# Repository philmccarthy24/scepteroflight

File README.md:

# Scepter of Light
## 3D printable prop

*Phil McCarthy, August 2021*

### What is this?
A 3D printed version of the Scepter of Light from Elena of Avalor, created by Phil McCarthy over summer 2021.

### Why?
My daughter loves Elena, and wanted a scepter to go with her costume. I've thought about designing a circuit board and doing some 3D printing for a while - so this was an ideal learning project with the right level of challenge. It took about three months to complete in my spare time.

The scepter lights up and plays music when turned on, and rumbles with "magic" when waved. See a quick [video demo here](https://youtu.be/RlnO9K1_UK8).

I've made [an Instructable](https://www.instructables.com/Scepter-of-Light/) and [a Thing](https://www.thingiverse.com/thing:4937785) to go with this repository, to make it more searchable.

### Features

- Easy access charging via MicroUSB port in unscrewable hilt - red light is charging, blue means charged. Grille around port allows heat dissapation during charge. 

- Custom PCB with ULN2003A driver allows independent control of each of the three side ultrabright LEDs, the top ultrabright LED array, and the vibration motor, via the MCU's output pins.

- All components on the PCB board are through-hole, allowing easy soldering/assembly, but it's thin enough to fit into the 50mm diameter scepter head.

- High spec Teensy 4.1 MCU with 600 MHz Cortex-M7 processor and 1MB RAM can support gesture recognition via ML (in future).

### What's included in this repository?
Original OpenSCAD designs and related assets for all parts, STL files for unmodified reprints (also Prusa project files which will save you time when slicing if you have a Prusa), KiCAD project files and gerbers for modifying/fabricating the PCB, and documentation.

Included in the documentation is [the full parts list](docs/BOM.md), [assembly instructions](docs/assembly.md), and [the printing settings that worked for me](docs/printing.md) when printing the parts out.

### Any gotchas?

I haven't included wav sound files for potential copyright reasons. You just need to find some appropriate sounds and save them as "theme.wav" and "blaze.wav" on the root of the micro SD card that slots into the microcontroller.

The GY-521 gyro module needs to be mounted onto the PCB upside down, due to a "feature" in the PCB design - this is documented in the assembly instructions.

The sound isn't super-loud. It's acceptably audible, but not room filling. This is because there's little space in the enclosure interior, so I had to opt for a thin 8ohm 0.5W 20mm speaker. As a result the default 9dB gain setting of the MAX98357 distorts the audio through this speaker. I reduced the gain to 6dB by connecting the GAIN pin to Vin, which results in non-distorted (but slightly quieter) audio.

If you have some way of mounting a larger, more powerful speaker (up to 3W), it's possible to get these different gain settings:  

- **15dB** if a 100K resistor is connected between **GAIN** and **GND**
- **12dB** if **GAIN** is connected directly to **GND**
- **9dB** if **GAIN** is not connected to anything
- **6dB** if **GAIN** is connected directly to **Vin** (default PCB wiring)
- **3dB** if a 100K resistor is connected between **GAIN** and **Vin**

You will need to hack the PCB with a craft knife and soldering iron or update the PCB design to achieve these changes.

### What's the future of the project?

I plan to add gesture recognition at some point - the MCU was chosen to be powerful enough to support machine learning and classification of accelerometer data.

I'm not sure when I'm going to get round to coding it in; it might be next year. If you want to implement this yourself, go for it - I'm excited to see what you do!

### Legal stuff
This project is a fan-made artistic prop, not a commercial product, and is free and open source. The PCB design, 3D print designs and MCU firmware are shared under the [GPLv3 license](https://www.gnu.org/licenses/gpl-3.0.en.html).

In particular note the warranty and liability sections - these designs are shared for you to do what you want with them, with the understanding that if they cause harm or damage to you, your property or your loved ones, **you and solely you take full responsibility**.

High capacity Lithium Ion batteries are **dangerous**, should *never* be short circuited, and must be used with care and knowledge. **Please don't assume my circuitry or designs are electrically or mechanically safe.**

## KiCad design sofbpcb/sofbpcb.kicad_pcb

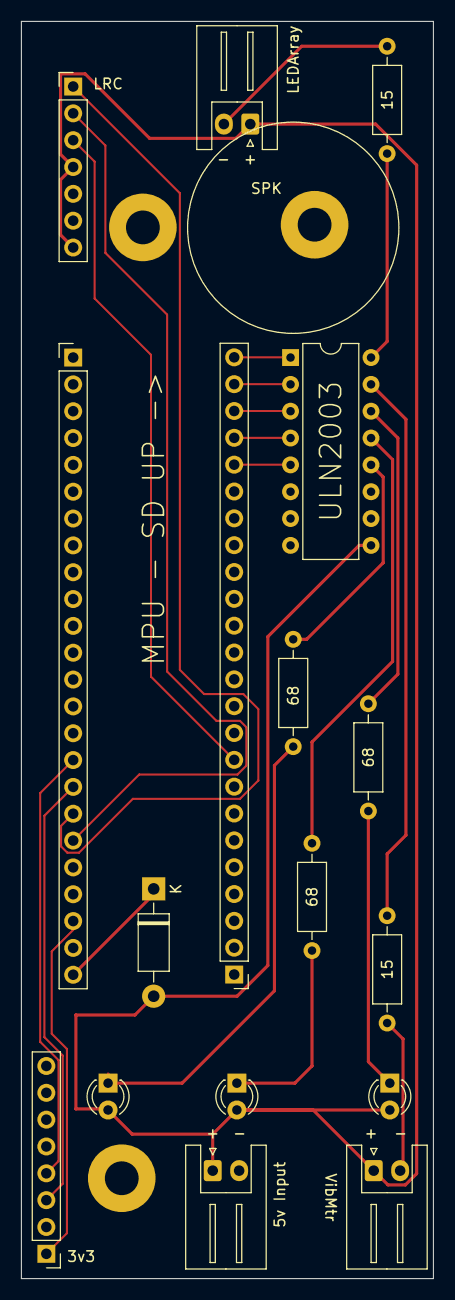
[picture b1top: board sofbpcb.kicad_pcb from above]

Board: 2 copper layers, 39.0 x 119.0 mm, 17 parts (0 on the bottom side), 24 nets.

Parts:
D1: D_Schottky; D_DO-41_SOD81_P10.16mm_Horizontal
D2, D3, D4: LED; LED_D3.0mm
J1: MAX98357A_hdr; PinHeader_1x07_P2.54mm_Vertical
J2: MPU6050_hdr; PinHeader_1x08_P2.54mm_Vertical
J3: 5v Power In; JST_XH_S2B-XH-A_1x02_P2.50mm_Horizontal
J4: LEDStalk_hdr; JST_XH_S2B-XH-A_1x02_P2.50mm_Horizontal
J5: VibrationMotor_hdr; JST_XH_S2B-XH-A_1x02_P2.50mm_Horizontal
J6: Teensy4.1_left_hdr; PinHeader_1x24_P2.54mm_Vertical
J7: Teensy4.1_right_hdr; PinHeader_1x24_P2.54mm_Vertical
R1, R5: 15; R_Axial_DIN0207_L6.3mm_D2.5mm_P10.16mm_Horizontal
R2, R3, R4: 68; R_Axial_DIN0207_L6.3mm_D2.5mm_P10.16mm_Horizontal
U2: ULN2003; DIP-16_W7.62mm

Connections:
+5V: D1.2, D2.2, D3.2, D4.2, J1.4, J1.7, J3.1, J4.1, J5.1, U2.9
/3v3: J2.1, J6.22
/BCLK: J1.2, J6.19
/DigAud: J1.3, J7.9
/GemLED1Sig: J7.22, U2.3
/GemLED2Sig: J7.21, U2.4
/GemLED3Sig: J7.20, U2.5
/LEDStalkSig: J7.24, U2.1
/LRCLK: J1.1, J6.18
/SCL: J2.3, J6.17
/SDA: J2.4, J6.16
/VIN: D1.1, J6.24
/VibMtrSig: J7.23, U2.2
GND: J1.6, J2.2, J3.2, J6.23, U2.8
unnamed: D2.1, R2.1
unnamed: D3.1, R3.1
unnamed: D4.1, R4.1
unnamed: J4.2, R1.1
unnamed: J5.2, R5.1
unnamed: R1.2, U2.16
unnamed: R2.2, U2.14
unnamed: R3.2, U2.13
unnamed: R4.2, U2.12
unnamed: R5.2, U2.15

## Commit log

2021-06-17 Prototype hilt and shaft, head mid-design
2021-06-22 Made shaft and hilt thinner, new battery module design
2021-06-22 MK3 battery module design
2021-06-29 Finished big diamond design and thistle mount body
2021-07-06 Gem, curls and thistle complete
2021-07-12 head prototyping
2021-07-15 Tweaks to head enclosure, circuit schematic complete
2021-07-15 Added teensy kicad lib
2021-07-15 Tweak to schematic pwr in
2021-07-15 Combined led stalk resistors into one
2021-07-18 pcb mid design. nearly there
2021-07-19 PCB design complete, just needs silk screen tidied up
2021-07-19 Added silk screen, plotted gerbers for pcb fab
2021-07-20 Tidying KiCad project folder
2021-07-20 GitIgnore KiCad temp files
2021-07-30 Fixes to head prior to first gold print
2021-08-08 Tidied up files and folders, added proper readme, started on assembly instructions
2021-08-18 Completed assembly instructions, fixes to STLs
2021-08-18 Reduced scepter photo size
2021-11-24 Made head thistle screw slightly longer
